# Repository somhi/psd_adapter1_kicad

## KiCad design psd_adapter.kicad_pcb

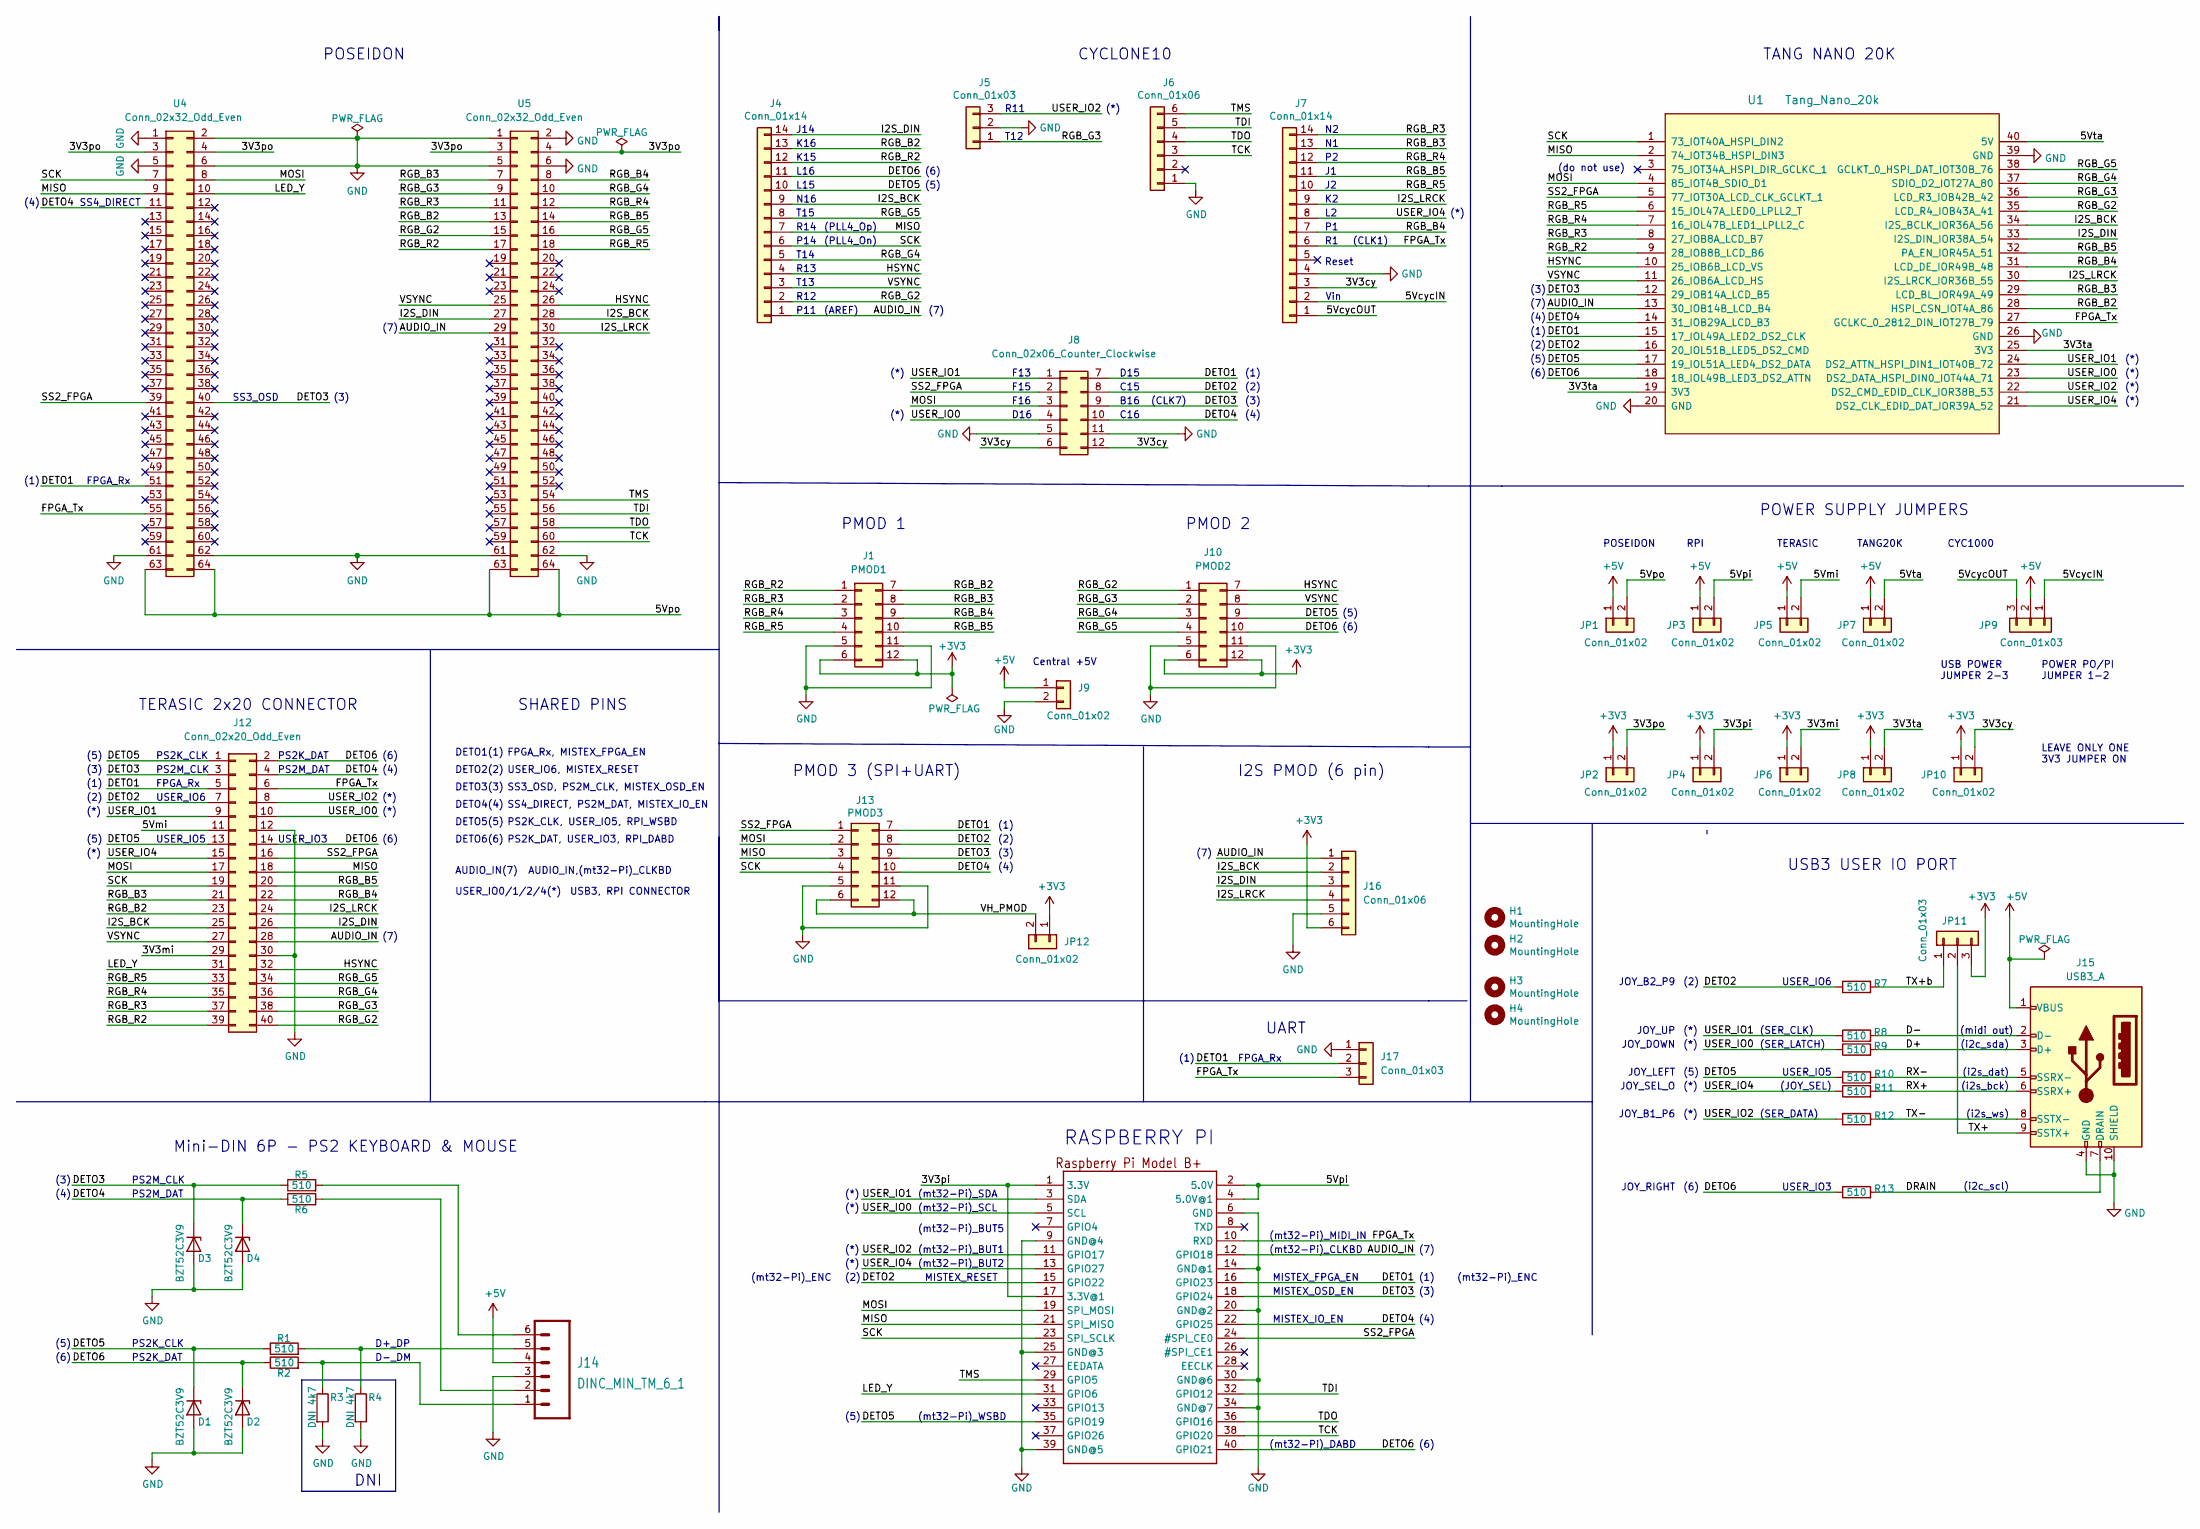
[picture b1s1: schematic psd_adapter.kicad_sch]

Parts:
D1, D2, D3, D4: BZT52C3V9; D_SOD-123
H1, H2, H3, H4: MountingHole; MountingHole_3.2mm_M3
J1: PMOD1; PMOD_Female_Horizontal_2
J4, J7: Conn_01x14; PinSocket_1x14_P2.54mm_Vertical
J5: Conn_01x03; PinSocket_1x03_P2.54mm_Vertical
J6, J16: Conn_01x06; PinSocket_1x06_P2.54mm_Vertical
J8: Conn_02x06_Counter_Clockwise; Pmod_2x06_P2.54mm_Vertical_2
J9: Conn_01x02; PinSocket_1x02_P2.54mm_Vertical
J10: PMOD2; PMOD_Female_Horizontal_2
J11: RASPBERRYPI_BPLUS_BONNETNODIM; PinSocket_2x20_P2.54mm_Vertical
J12: Conn_02x20_Odd_Even; PinHeader_2x20_P2.54mm_Vertical
J13: PMOD3; PMOD_Female_Horizontal_2
J14: DINC_MIN_TM_6_1; DINC_MIN_TM_6_1PRIMARY
J15: USB3_A; USB-3.0-TH_C69073
J17: Conn_01x03; PinHeader_1x03_P2.54mm_Vertical
JP1, JP2, JP3, JP4, JP5, JP6, JP7, JP8, JP10, JP12: Conn_01x02; PinHeader_1x02_P2.54mm_Vertical
JP9, JP11: Conn_01x03; PinHeader_1x03_P2.54mm_Vertical
R1, R2, R5, R6, R7, R8, R9, R10, R11, R12, R13: 510; R_0805_2012Metric_Pad1.20x1.40mm_HandSolder
R3, R4: DNI 4k7; R_0805_2012Metric_Pad1.20x1.40mm_HandSolder
U1: Tang_Nano_20k
U4, U5: Conn_02x32_Odd_Even; PinHeader_2x32_P2.54mm_Vertical

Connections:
+3V3: J1.6, J1.12, J10.6, J10.12, J16.6, JP2.1, JP4.1, JP6.1, JP8.1, JP10.1, JP11.3, JP12.1
+5V: J9.1, J14.4, J15.1 (VBUS), JP1.1, JP3.1, JP5.1, JP7.1, JP9.2
/3V3cy: J7.3, J8.6, J8.12, JP10.2
/3V3mi: J12.29, JP6.2
/3V3pi: J11.1 (3.3V), J11.17 (3.3V@1), JP4.2
/3V3po: JP2.2, U4.3, U4.4, U5.3, U5.4
/3V3ta: JP8.2, U1.19 (3V3), U1.25 (3V3)
/5VcycIN: J7.2, JP9.1
/5VcycOUT: J7.1, JP9.3
/5Vmi: J12.11, JP5.2
/5Vpi: J11.2 (5.0V), J11.4 (5.0V@1), JP3.2
/5Vpo: JP1.2, U4.63, U4.64, U5.63, U5.64
/5Vta: JP7.2, U1.40 (5V)
/AUDIO_IN: J4.1, J11.12 (GPIO18), J12.28, J16.1, U1.13 (30_IOB14B_LCD_B4), U5.29
/D+: J15.3 (D+), R9.2
/D-: J15.2 (D-), R8.2
/DETO1: J8.7, J11.16 (GPIO23), J12.5, J13.7, J17.2, U1.15 (17_IOL49A_LED2_DS2_CLK), U4.51
/DETO2: J8.8, J11.15 (GPIO22), J12.7, J13.8, R7.1, U1.16 (20_IOL51B_LED5_DS2_CMD)
/DETO3: D3.1 (K), J8.9, J11.18 (GPIO24), J12.3, J13.9, R5.1, U1.12 (29_IOB14A_LCD_B5), U4.40
/DETO4: D4.1 (K), J8.10, J11.22 (GPIO25), J12.4, J13.10, R6.1, U1.14 (31_IOB29A_LCD_B3), U4.11
/DETO5: D1.1 (K), J4.10, J10.9, J11.35 (GPIO19), J12.1, J12.13, R1.1, R10.1, U1.17 (19_IOL51A_LED4_DS2_DATA)
/DETO6: D2.1 (K), J4.11, J10.10, J11.40 (GPIO21), J12.2, J12.14, R2.1, R13.1, U1.18 (18_IOL49B_LED3_DS2_ATTN)
/DRAIN: J15.7 (DRAIN), R13.2
/FPGA_Tx: J7.6, J11.10 (RXD), J12.6, J17.3, U1.27 (GCLKC_0_2812_DIN_IOT27B_79), U4.55
/HSYNC: J4.4, J10.7, J12.32, U1.10 (25_IOB6B_LCD_VS), U5.26
/I2S_BCK: J4.9, J12.25, J16.2, U1.34 (I2S_BCLK_IOR36A_56), U5.28
/I2S_DIN: J4.14, J12.26, J16.3, U1.33 (I2S_DIN_IOR38A_54), U5.27
/I2S_LRCK: J7.9, J12.24, J16.4, U1.30 (I2S_LRCK_IOR36B_55), U5.30
/LED_Y: J11.31 (GPIO6), J12.31, U4.10
/MISO: J4.7, J11.21 (SPI_MISO), J12.18, J13.3, U1.2 (74_IOT34B_HSPI_DIN3), U4.9
/MOSI: J8.3, J11.19 (SPI_MOSI), J12.17, J13.2, U1.4 (85_IOT4B_SDIO_D1), U4.8
/RGB_B2: J1.7, J4.13, J12.23, U1.28 (HSPI_CSN_IOT4A_86), U5.13
/RGB_B3: J1.8, J7.13, J12.21, U1.29 (LCD_BL_IOR49A_49), U5.7
/RGB_B4: J1.9, J7.7, J12.22, U1.31 (LCD_DE_IOR49B_48), U5.8
/RGB_B5: J1.10, J7.11, J12.20, U1.32 (PA_EN_IOR45A_51), U5.14
/RGB_G2: J4.2, J10.1, J12.40, U1.35 (LCD_R4_IOB43A_41), U5.15
/RGB_G3: J5.1, J10.2, J12.38, U1.36 (LCD_R3_IOB42B_42), U5.9
/RGB_G4: J4.5, J10.3, J12.36, U1.37 (SDIO_D2_IOT27A_80), U5.10
/RGB_G5: J4.8, J10.4, J12.34, U1.38 (GCLKT_0_HSPI_DAT_IOT30B_76), U5.16
/RGB_R2: J1.1, J4.12, J12.39, U1.9 (28_IOB8B_LCD_B6), U5.17
/RGB_R3: J1.2, J7.14, J12.37, U1.8 (27_IOB8A_LCD_B7), U5.11
/RGB_R4: J1.3, J7.12, J12.35, U1.7 (16_IOL47B_LED1_LPLL2_C), U5.12
/RGB_R5: J1.4, J7.10, J12.33, U1.6 (15_IOL47A_LED0_LPLL2_T), U5.18
/RX+: J15.6 (SSRX+), R11.2
/RX-: J15.5 (SSRX-), R10.2
/SCK: J4.6, J11.23 (SPI_SCLK), J12.19, J13.4, U1.1 (73_IOT40A_HSPI_DIN2), U4.7
/SS2_FPGA: J8.2, J11.24 (#SPI_CE0), J12.16, J13.1, U1.5 (77_IOT30A_LCD_CLK_GCLKT_1), U4.39
/TCK: J6.3, J11.38 (GPIO20), U5.60
/TDI: J6.5, J11.32 (GPIO12), U5.56
/TDO: J6.4, J11.36 (GPIO16), U5.58
/TMS: J6.6, J11.29 (GPIO5), U5.54
/TX+: J15.9 (SSTX+), JP11.2
/TX+b: JP11.1, R7.2
/TX-: J15.8 (SSTX-), R12.2
/USER_IO0: J8.4, J11.5 (SCL), J12.10, R9.1, U1.23 (DS2_DATA_HSPI_DIN0_IOT44A_71)
/USER_IO1: J8.1, J11.3 (SDA), J12.9, R8.1, U1.24 (DS2_ATTN_HSPI_DIN1_IOT40B_72)
/USER_IO2: J5.3, J11.11 (GPIO17), J12.8, R12.1, U1.22 (DS2_CMD_EDID_CLK_IOR38B_53)
/USER_IO4: J7.8, J11.13 (GPIO27), J12.15, R11.1, U1.21 (DS2_CLK_EDID_DAT_IOR39A_52)
/VH_PMOD: J13.6, J13.12, JP12.2
/VSYNC: J4.3, J10.8, J12.27, U1.11 (26_IOB6A_LCD_HS), U5.25
GND: D1.2 (A), D2.2 (A), D3.2 (A), D4.2 (A), J1.5, J1.11, J5.2, J6.1, J7.4, J8.5, J8.11, J9.2, J10.5, J10.11, J11.6 (GND), J11.9 (GND@4), J11.14 (GND@1), J11.20 (GND@2), J11.25 (GND@3), J11.30 (GND@6), J11.34 (GND@7), J11.39 (GND@5), J12.12, J12.30, J13.5, J13.11, J14.3, J15.4 (GND), J15.10 (SHIELD), J16.5, J17.1, R3.2, R4.2, U1.20 (GND), U1.26 (GND), U1.39 (GND), U4.1, U4.2, U4.5, U4.6, U4.61, U4.62, U5.1, U5.2, U5.5, U5.6, U5.61, U5.62
unnamed: J14.1, R2.2, R3.1
unnamed: J14.2, R6.2
unnamed: J14.5, R1.2, R4.1
unnamed: J14.6, R5.2

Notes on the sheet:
SS3_OSD
(4)
(i2s_bck)
F16
JOY_DOWN
(i2c_sda)
USER_IO3
(3)
(1)
(6)
(mt32-Pi)_BUT1
(5)
R11
(*)
PMOD 2
(mt32-Pi)_SDA
JOY_SEL_O
UART
(do not use)
MISTEX_IO_EN
(2)
USB3, RPI CONNECTOR
D16
DETO1(1)
(SER_CLK)
(mt32-Pi)_DABD
FPGA_Rx
RASPBERRY PI
PS2M_DAT
N16
(i2s_ws)
PS2M_CLK
TERASIC 2x20 CONNECTOR
USER_IO5
T13
SS4_DIRECT, PS2M_DAT, MISTEX_IO_EN
D15
POWER PO/PI JUMPER 1-2
K16
PS2K_CLK

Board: 2 copper layers, 52 parts (0 on the bottom side), 65 nets, no tracks yet.

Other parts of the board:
LO2: OSHW-Logo2_14.6x12mm_SilkScreen

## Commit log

2024-01-09 schematic done
